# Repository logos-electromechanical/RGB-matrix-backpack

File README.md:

Logos RGB Matrix Backpack firmware, examples and docs
---------------------------

With the default firmware, this backpack is a board for driving 8x8 common anode RGB LED matrices from the I2C bus.

Remember that firmware memory is precious - you have *2 KB* of EEPROM and *128 bytes* of SRAM to work with on the backpack itself.

**Compilers:**

* AVR firmware is compiled with [WinAVR v20100110](http://sourceforge.net/projects/winavr/)

* Examples are compiled with [the Arduino IDE](http://arduino.cc/en/main/software)

**Hardware info:**

* [Holtek LED driver - HT1632C data sheet, FAQs and app notes](http://www.holtek.com/english/docum/consumer/1632c.htm)
	
* [Atmel MCU - ATtiny 2313V data sheet](http://www.atmel.com/Images/doc2543.pdf)

* [RGB LED common anode 8x8 matrix - ORM 2088RGB-5 data sheet](http://selfbuilt.net/datasheets/2088RGB-5-datasheet.jpg)

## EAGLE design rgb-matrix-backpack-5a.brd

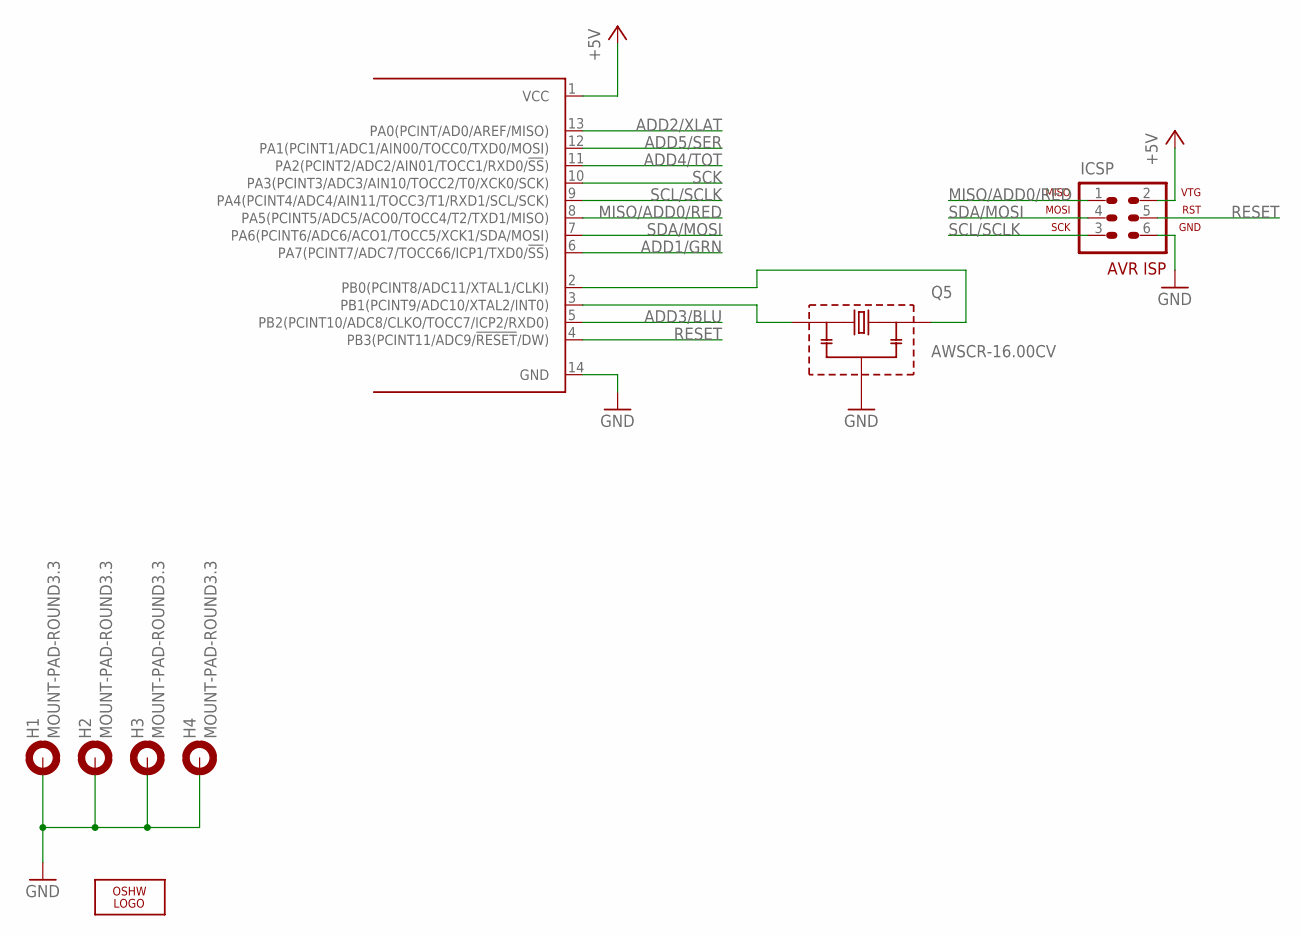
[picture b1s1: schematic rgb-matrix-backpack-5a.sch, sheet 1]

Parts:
H1, H2, H3, H4: MOUNT-PAD-ROUND3.3; 3,3-PAD
ICSP: AVR-ISP-6
LOGO1: OSHW_LOGO_FILLX0350-NT; OSHW_FILLX350_NOTEXT
Q5: AWSCR-16.00CV; AWSCR
U1: ATTINY841-SU; SO14

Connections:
ADD1/GRN: U1.6 (PA7(PCINT7/ADC7/TOCC66/ICP1/TXD0/!SS!)); also elsewhere on the board
ADD2/XLAT: U1.13 (PA0(PCINT/AD0/AREF/MISO)); also elsewhere on the board
ADD3/BLU: U1.5 (PB2(PCINT10/ADC8/CLKO/TOCC7/ICP2/RXD0)); also elsewhere on the board
ADD4/TOT: U1.11 (PA2(PCINT2/ADC2/AIN01/TOCC1/RXD0/!SS!)); also elsewhere on the board
ADD5/SER: U1.12 (PA1(PCINT1/ADC1/AIN00/TOCC0/TXD0/MOSI)); also elsewhere on the board
GND: H1.B3,3, H2.B3,3, H3.B3,3, H4.B3,3, ICSP.6, Q5.2, U1.14 (GND); also elsewhere on the board
MISO/ADD0/RED: ICSP.1, U1.8 (PA5(PCINT5/ADC5/ACO0/TOCC4/T2/TXD1/MISO)); also elsewhere on the board
unnamed: Q5.1, U1.3 (PB1(PCINT9/ADC10/XTAL2/INT0))
unnamed: Q5.3, U1.2 (PB0(PCINT8/ADC11/XTAL1/CLKI))
RESET: ICSP.5, U1.4 (PB3(PCINT11/ADC9/!RESET!/DW))
SCK: U1.10 (PA3(PCINT3/ADC3/AIN10/TOCC2/T0/XCK0/SCK)); also elsewhere on the board
SCL/SCLK: ICSP.3, U1.9 (PA4(PCINT4/ADC4/AIN11/TOCC3/T1/RXD1/SCL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); also elsewhere on the board
SDA/MOSI: ICSP.4, U1.7 (PA6(PCINT6/ADC6/ACO1/TOCC5/XCK1/SDA/MOS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); also elsewhere on the board
VCC: ICSP.2, U1.1 (VCC); also elsewhere on the board

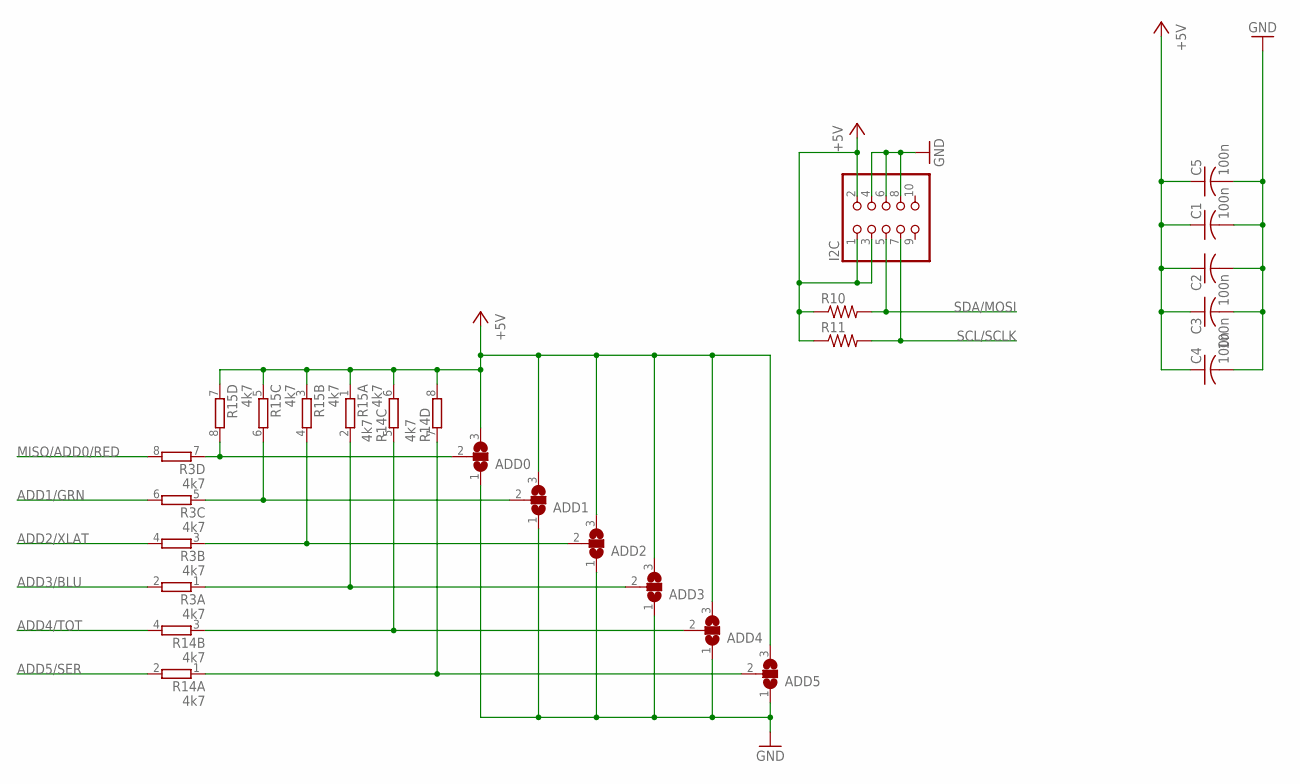
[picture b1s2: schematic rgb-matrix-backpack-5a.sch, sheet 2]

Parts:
ADD0, ADD1, ADD2, ADD3, ADD4, ADD5: SJ2W; SJ_2
C1, C2, C4, C5: 100n; C0603; PARTNO CC0603MRY5V9BB104
C3: 100n; C0603; PARTNO CC0603ZRY5V7BB105
I2C: PINHD-2X5_2.54-90°; 2X05/90
R3, R14, R15: 4k7; CTS742C083-RES; PARTNO 742C083102JPTR
R10, R11: R-US_0207/2V; 0207/2V; PARTNO CF14JT4K70

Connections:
ADD1/GRN: R3.6 (2); also elsewhere on the board
ADD2/XLAT: R3.4 (2); also elsewhere on the board
ADD3/BLU: R3.2; also elsewhere on the board
ADD4/TOT: R14.4 (2); also elsewhere on the board
ADD5/SER: R14.2; also elsewhere on the board
GND: ADD0.1, ADD1.1, ADD2.1, ADD3.1, ADD4.1, ADD5.1, C1.2, C2.2, C3.2, C4.2, C5.2, I2C.4, I2C.6, I2C.8; also elsewhere on the board
MISO/ADD0/RED: R3.8 (2); also elsewhere on the board
unnamed: ADD3.2, R3.1, R15.2
unnamed: ADD2.2, R3.3 (1), R15.4 (2)
unnamed: ADD0.2, R3.7 (1), R15.8 (2)
unnamed: ADD1.2, R3.5 (1), R15.6 (2)
unnamed: ADD4.2, R14.3 (1), R14.5 (1)
unnamed: ADD5.2, R14.1, R14.7 (1)
SCL/SCLK: I2C.7, R11.2; also elsewhere on the board
SDA/MOSI: I2C.5, R10.2; also elsewhere on the board
VCC: ADD0.3, ADD1.3, ADD2.3, ADD3.3, ADD4.3, ADD5.3, C1.1, C2.1, C3.1, C4.1, C5.1, I2C.1, I2C.2, I2C.3, R10.1, R11.1, R14.6 (2), R14.8 (2), R15.1, R15.3 (1), R15.5 (1), R15.7 (1); also elsewhere on the board

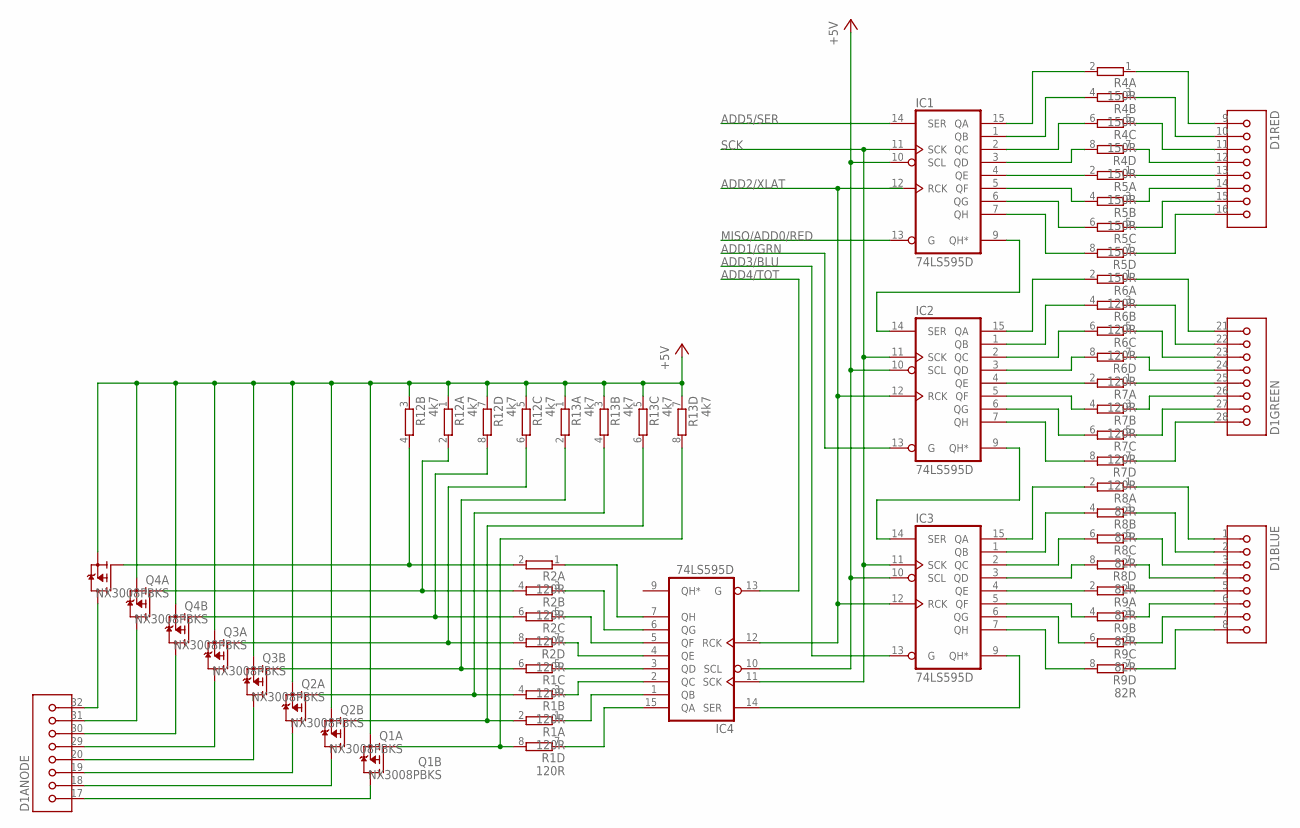
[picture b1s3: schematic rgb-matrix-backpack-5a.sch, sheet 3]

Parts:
D1: 60MM-8X8-RGB-LED-ARRAY; 60MM-8X8-RGB-MATRIX
IC1, IC2, IC3, IC4: 74LS595D; SO16
Q1: NX3008PBKS; SOT363_INFINEON; PARTNO NX3008PBKS
Q2, Q3, Q4: NX3008PBKS; SOT363_INFINEON
R1, R2, R6, R7: 120R; CTS742C083-RES; PARTNO 742C083102JPTR
R4, R5: 150R; CTS742C083-RES; PARTNO 742C083102JPTR
R8, R9: 82R; CTS742C083-RES; PARTNO 742C083102JPTR
R12, R13: 4k7; CTS742C083-RES; PARTNO 742C083102JPTR

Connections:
ADD1/GRN: IC2.13 (G); also elsewhere on the board
ADD2/XLAT: IC1.12 (RCK), IC2.12 (RCK), IC3.12 (RCK), IC4.12 (RCK); also elsewhere on the board
ADD3/BLU: IC3.13 (G); also elsewhere on the board
ADD4/TOT: IC4.13 (G); also elsewhere on the board
ADD5/SER: IC1.14 (SER); also elsewhere on the board
GND: IC1.8 (GND), IC2.8 (GND), IC3.8 (GND), IC4.8 (GND); also elsewhere on the board
MISO/ADD0/RED: IC1.13 (G); also elsewhere on the board
unnamed: D1.9 (1), R4.1
unnamed: D1.10 (2), R4.3 (1)
unnamed: D1.11 (3), R4.5 (1)
unnamed: D1.12 (4), R4.7 (1)
unnamed: D1.13 (5), R5.1
unnamed: D1.14 (6), R5.3 (1)
unnamed: D1.15 (7), R5.5 (1)
unnamed: D1.16 (8), R5.7 (1)
unnamed: D1.1, R8.1
unnamed: D1.2, R8.3 (1)
unnamed: D1.3, R8.5 (1)
unnamed: D1.4, R8.7 (1)
unnamed: D1.5, R9.1
unnamed: D1.6, R9.3 (1)
unnamed: D1.7, R9.5 (1)
unnamed: D1.8, R9.7 (1)
unnamed: D1.21 (8), R6.1
unnamed: D1.22 (7), R6.3 (1)
unnamed: D1.23 (6), R6.5 (1)
unnamed: D1.24 (5), R6.7 (1)
unnamed: D1.25 (4), R7.1
unnamed: D1.26 (3), R7.3 (1)
unnamed: D1.27 (2), R7.5 (1)
unnamed: D1.28 (1), R7.7 (1)
unnamed: IC3.9 (QH*), IC4.14 (SER)
unnamed: IC1.15 (QA), R4.2
unnamed: IC1.2 (QC), R4.6 (2)
unnamed: IC1.4 (QE), R5.2
unnamed: IC1.6 (QG), R5.6 (2)
unnamed: IC2.15 (QA), R6.2
unnamed: IC2.2 (QC), R6.6 (2)
unnamed: IC2.4 (QE), R7.2
unnamed: IC2.6 (QG), R7.6 (2)
unnamed: IC3.1 (QB), R8.4 (2)
unnamed: IC3.3 (QD), R8.8 (2)
unnamed: IC3.5 (QF), R9.4 (2)
unnamed: IC3.7 (QH), R9.8 (2)
unnamed: IC1.3 (QD), R4.8 (2)
unnamed: IC1.5 (QF), R5.4 (2)
unnamed: IC2.1 (QB), R6.4 (2)
unnamed: IC2.3 (QD), R6.8 (2)
unnamed: IC2.5 (QF), R7.4 (2)
unnamed: IC2.7 (QH), R7.8 (2)
unnamed: IC3.15 (QA), R8.2
unnamed: IC3.2 (QC), R8.6 (2)
unnamed: IC3.4 (QE), R9.2
unnamed: IC3.6 (QG), R9.6 (2)
unnamed: IC4.15 (QA), R1.7 (1)
unnamed: IC4.1 (QB), R1.1
unnamed: IC4.2 (QC), R1.3 (1)
unnamed: IC4.3 (QD), R1.5 (1)
unnamed: Q1.5 (G), R1.8 (2), R13.8 (2)
unnamed: IC1.7 (QH), R5.8 (2)
unnamed: Q1.2 (G), R1.2, R13.6 (2)
unnamed: IC1.9 (QH*), IC2.14 (SER)
unnamed: IC2.9 (QH*), IC3.14 (SER)
unnamed: Q2.2 (G), R1.6 (2), R13.2
unnamed: Q2.5 (G), R1.4 (2), R13.4 (2)
unnamed: IC1.1 (QB), R4.4 (2)
unnamed: D1.20 (4), Q2.6 (D)
unnamed: D1.19 (3), Q2.3 (D)
unnamed: D1.18 (2), Q1.6 (D)
unnamed: D1.17 (1), Q1.3 (D)
unnamed: D1.29 (5), Q3.3 (D)
unnamed: D1.30 (6), Q3.6 (D)
unnamed: D1.31 (7), Q4.3 (D)
unnamed: D1.32 (8), Q4.6 (D)
unnamed: IC4.4 (QE), R2.7 (1)
unnamed: IC4.5 (QF), R2.5 (1)
unnamed: IC4.6 (QG), R2.3 (1)
unnamed: IC4.7 (QH), R2.1
unnamed: Q4.2 (G), R2.2, R12.4 (2)
unnamed: Q4.5 (G), R2.4 (2), R12.2
unnamed: Q3.2 (G), R2.6 (2), R12.8 (2)
unnamed: Q3.5 (G), R2.8 (2), R12.6 (2)
SCK: IC1.11 (SCK), IC2.11 (SCK), IC3.11 (SCK), IC4.11 (SCK); also elsewhere on the board
VCC: IC1.10 (SCL), IC1.16 (VCC), IC2.10 (SCL), IC2.16 (VCC), IC3.10 (SCL), IC3.16 (VCC), IC4.10 (SCL), IC4.16 (VCC), Q1.1 (S), Q1.4 (S), Q2.1 (S), Q2.4 (S), Q3.1 (S), Q3.4 (S), Q4.1 (S), Q4.4 (S), R12.1, R12.3 (1), R12.5 (1), R12.7 (1), R13.1, R13.3 (1), R13.5 (1), R13.7 (1); also elsewhere on the board

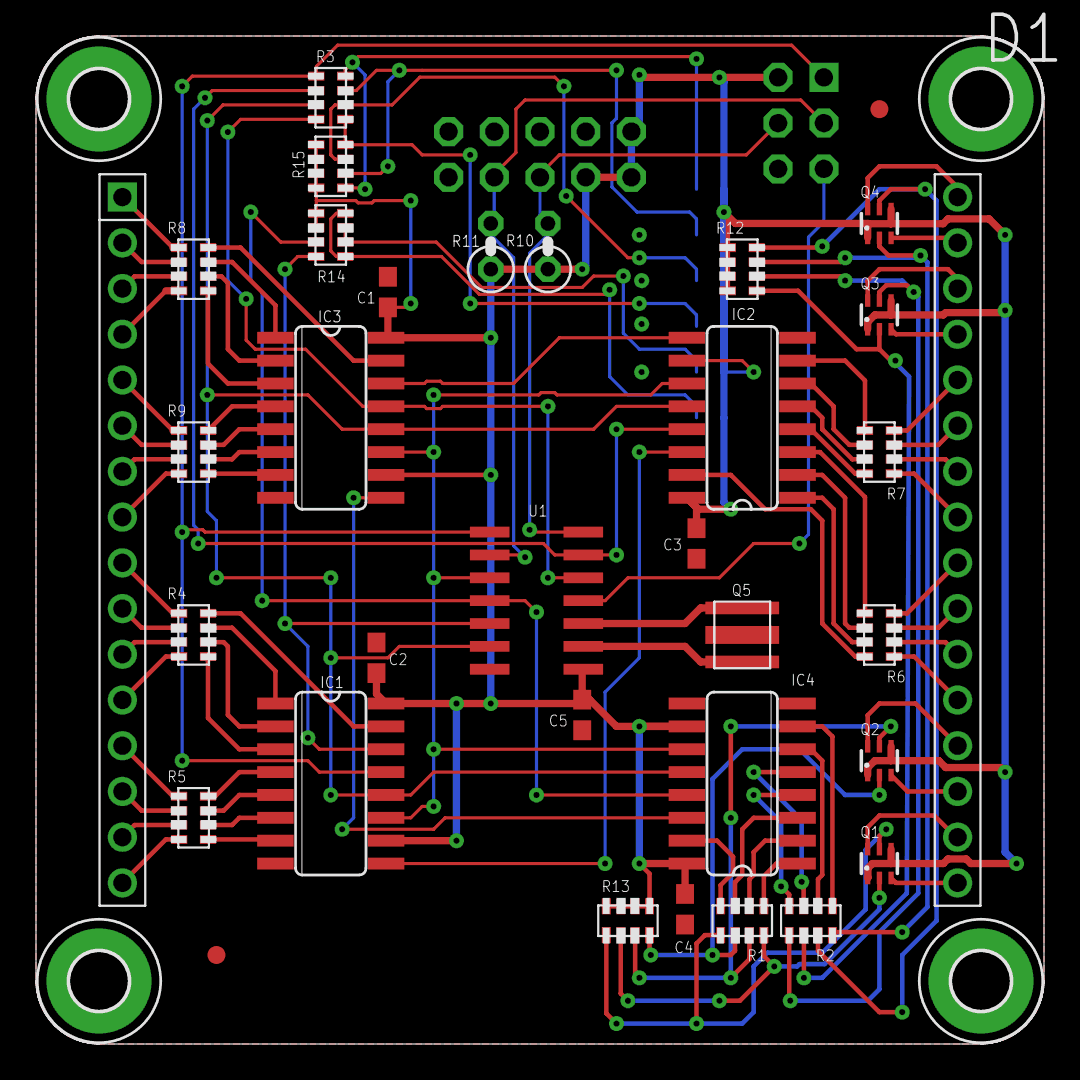
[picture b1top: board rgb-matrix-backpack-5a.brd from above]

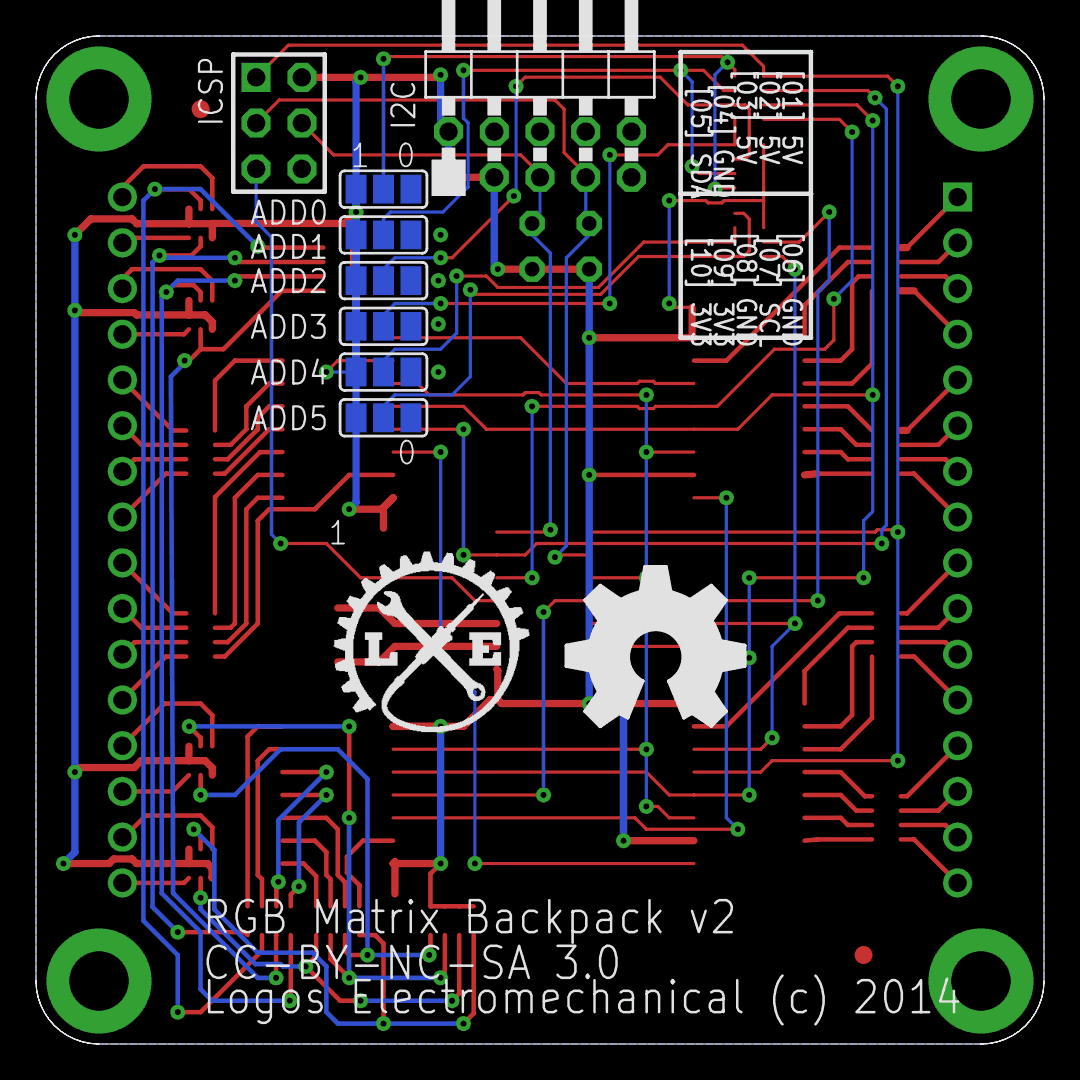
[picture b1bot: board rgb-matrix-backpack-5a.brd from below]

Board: 2 copper layers, 56.0 x 56.0 mm, 47 parts (10 on the bottom side), 95 nets.

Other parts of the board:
U$1: LOGO-SM
U$4, U$5: FIDUCIAL_G10

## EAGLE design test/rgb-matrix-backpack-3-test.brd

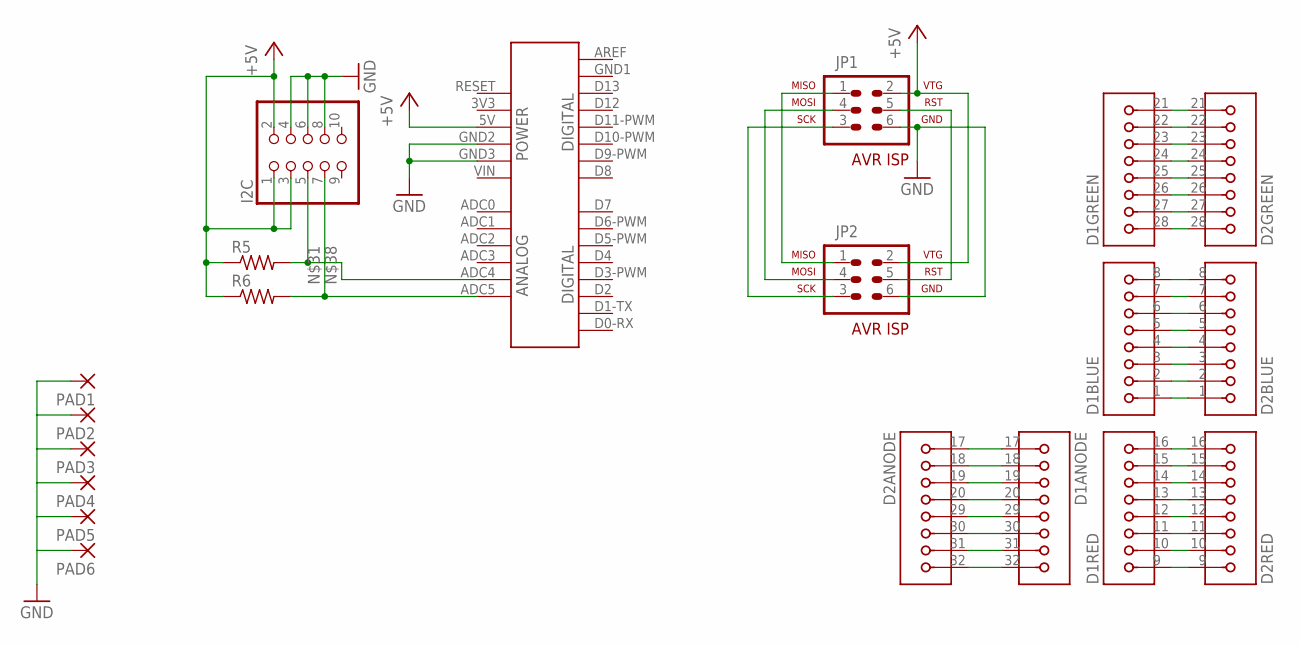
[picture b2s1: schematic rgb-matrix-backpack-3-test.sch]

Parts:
D1, D2: 60MM-8X8-RGB-LED-ARRAY; 60MM-8X8-RGB-MATRIX
I2C: PINHD-2X5_2.54-90°; 2X05/90
JP1, JP2: AVR-ISP-6
PAD1, PAD2, PAD3, PAD4, PAD5, PAD6: 1,6/0,8
R5, R6: R-US_R0603; R0603
SHIELD1: 2009

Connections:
+5V: I2C.1, I2C.2, I2C.3, JP1.2, JP2.2, R5.1, R6.1, SHIELD1.5V
GND: I2C.4, I2C.6, I2C.8, JP1.6, JP2.6, PAD1.1, PAD2.1, PAD3.1, PAD4.1, PAD5.1, PAD6.1, SHIELD1.GND2, SHIELD1.GND3
unnamed: D1.17 (1), D2.17 (1)
unnamed: D1.18 (2), D2.18 (2)
unnamed: D1.19 (3), D2.19 (3)
unnamed: D1.20 (4), D2.20 (4)
unnamed: D1.29 (5), D2.29 (5)
unnamed: D1.30 (6), D2.30 (6)
unnamed: D1.31 (7), D2.31 (7)
unnamed: D1.32 (8), D2.32 (8)
unnamed: D1.1, D2.1
unnamed: D1.2, D2.2
unnamed: D1.3, D2.3
unnamed: D1.4, D2.4
unnamed: D1.5, D2.5
unnamed: D1.6, D2.6
unnamed: D1.7, D2.7
unnamed: D1.8, D2.8
unnamed: D1.9 (1), D2.9 (1)
unnamed: D1.10 (2), D2.10 (2)
unnamed: D1.11 (3), D2.11 (3)
unnamed: D1.12 (4), D2.12 (4)
unnamed: D1.13 (5), D2.13 (5)
unnamed: D1.14 (6), D2.14 (6)
unnamed: D1.15 (7), D2.15 (7)
unnamed: D1.16 (8), D2.16 (8)
unnamed: D1.28 (1), D2.28 (1)
unnamed: D1.27 (2), D2.27 (2)
unnamed: D1.26 (3), D2.26 (3)
unnamed: JP1.1, JP2.1
unnamed: D1.25 (4), D2.25 (4)
unnamed: D1.24 (5), D2.24 (5)
unnamed: I2C.5, R5.2, SHIELD1.ADC4
unnamed: D1.23 (6), D2.23 (6)
unnamed: D1.22 (7), D2.22 (7)
unnamed: D1.21 (8), D2.21 (8)
unnamed: JP1.5, JP2.5
unnamed: I2C.7, R6.2, SHIELD1.ADC5
SCL: JP1.3, JP2.3
SDA: JP1.4, JP2.4

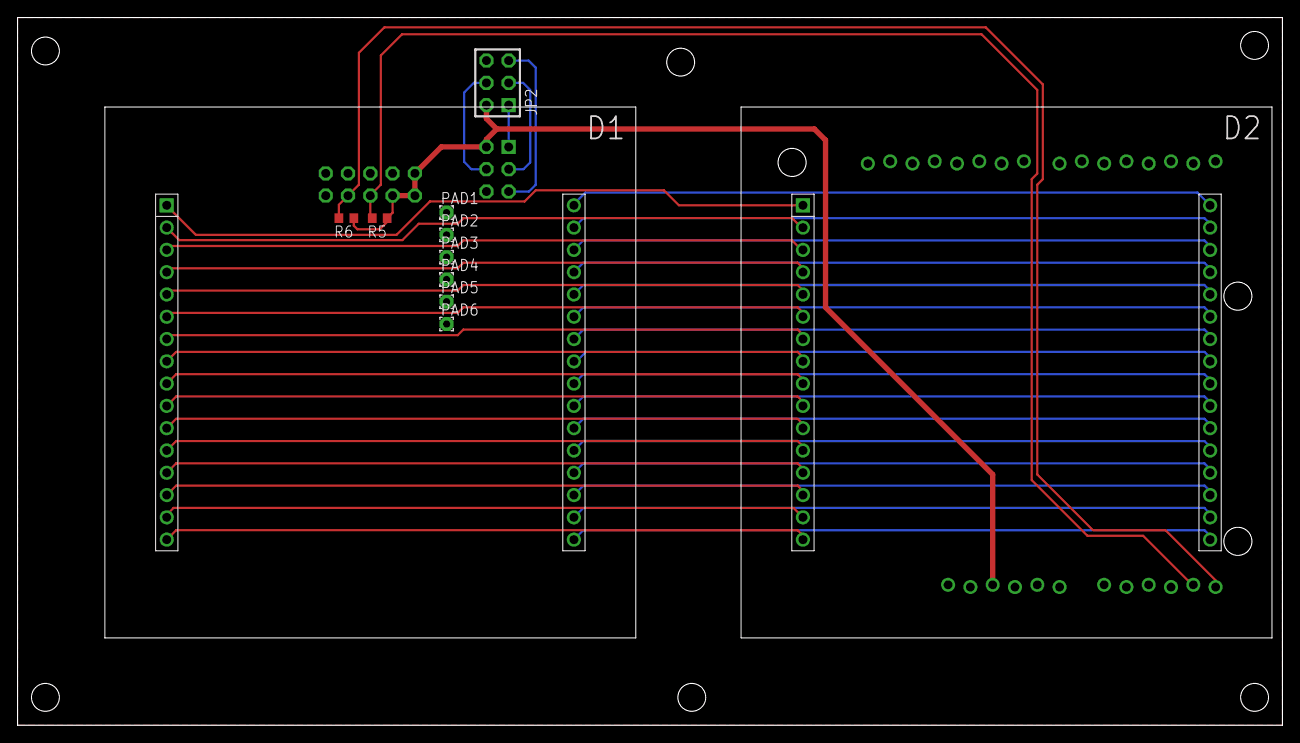
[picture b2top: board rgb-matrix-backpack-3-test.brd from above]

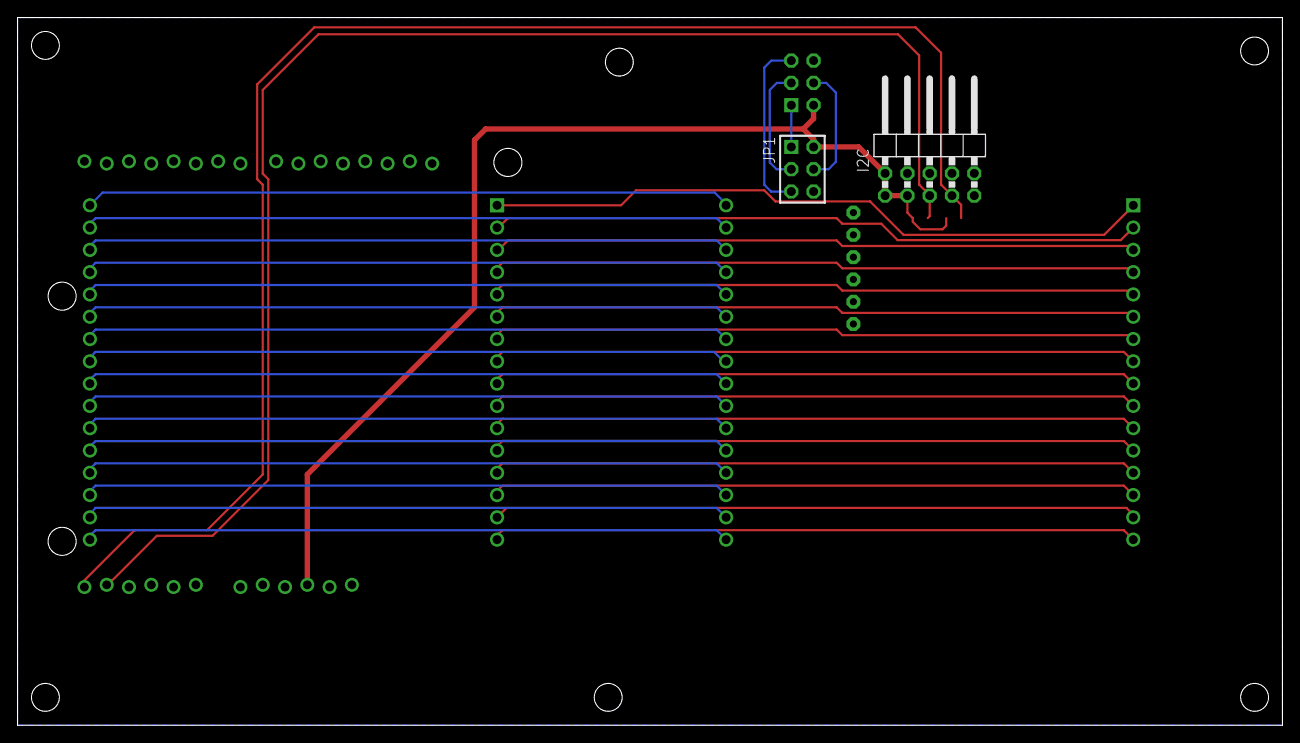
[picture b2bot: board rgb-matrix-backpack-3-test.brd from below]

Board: 2 copper layers, 144.1 x 80.6 mm, 14 parts (2 on the bottom side), 40 nets.

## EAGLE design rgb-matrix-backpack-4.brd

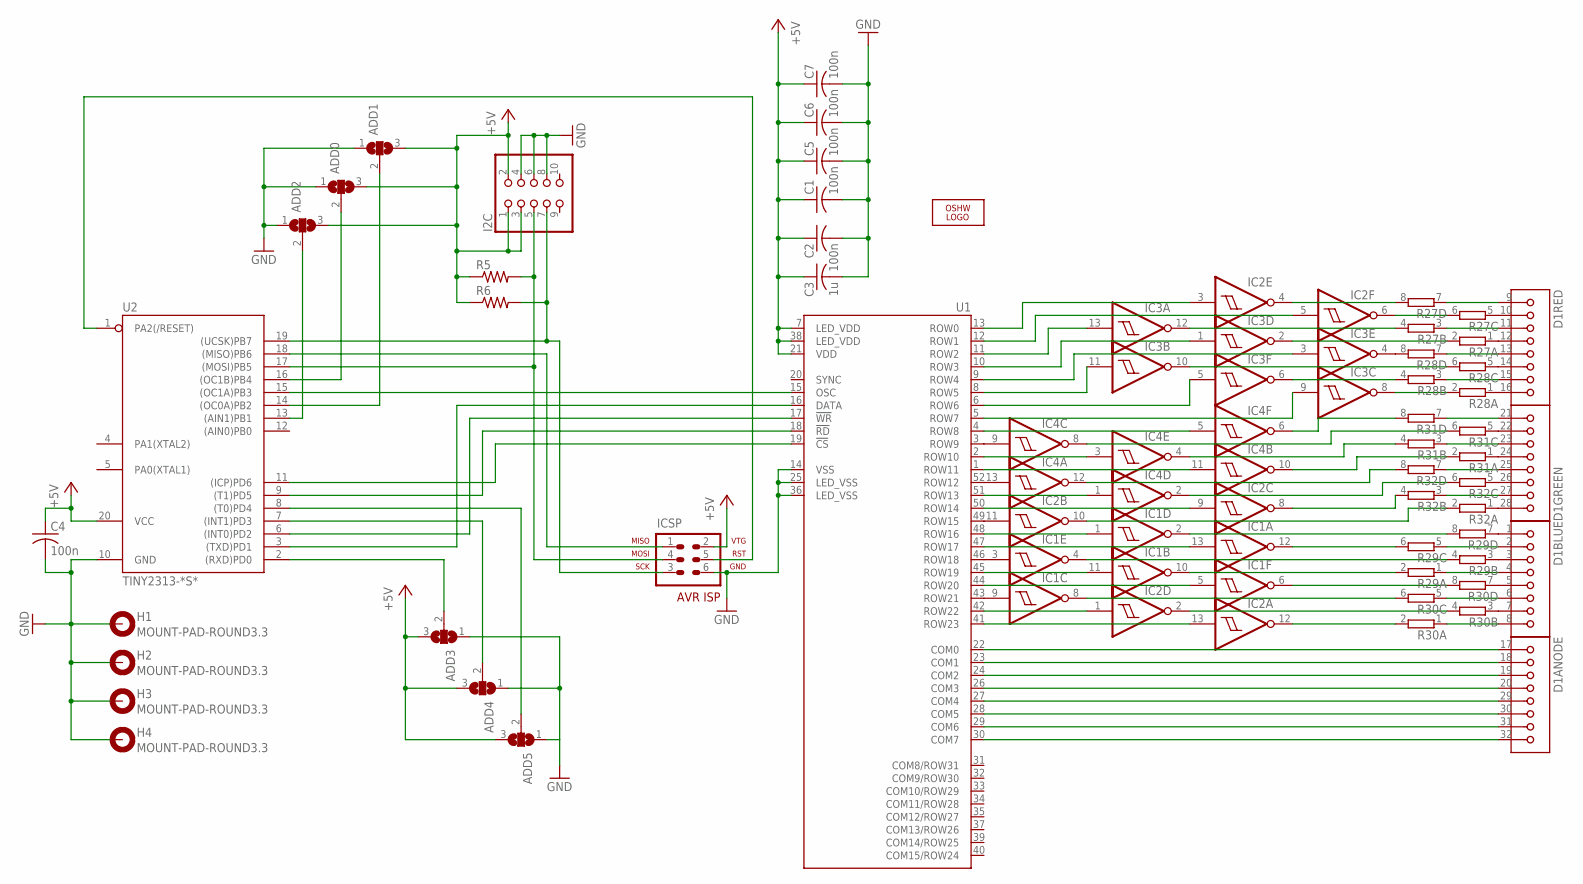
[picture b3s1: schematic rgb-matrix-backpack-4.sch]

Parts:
ADD0, ADD1, ADD2, ADD3, ADD4, ADD5: SJ2W; SJ_2
C1, C2, C4, C5, C6, C7: 100n; C0603; PARTNO CC0603MRY5V9BB104
C3: 1u; C0603; PARTNO CC0603ZRY5V7BB105
D1: 60MM-8X8-RGB-LED-ARRAY; 60MM-8X8-RGB-MATRIX
H1, H2, H3, H4: MOUNT-PAD-ROUND3.3; 3,3-PAD
I2C: PINHD-2X5_2.54-90°; 2X05/90
IC1, IC2, IC3, IC4: 74AC14D; SO14; PARTNO SN74AC14D
ICSP: AVR-ISP-6
LOGO1: OSHW_LOGO_FILLX0350-NT; OSHW_FILLX350_NOTEXT
R5, R6: R-US_0207/2V; 0207/2V; PARTNO CF14JT4K70
R27, R28, R29, R30, R31, R32: 4R-NCTS742C083; CTS742C083-RES; PARTNO 742C083102JPTR
U1: HT1632C; QFP52_SOT379-1; PARTNO HT1632C
U2: TINY2313-*S*; SO20L$; PARTNO ATTINY2313V-10SU

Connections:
GND: ADD0.1, ADD1.1, ADD2.1, ADD3.1, ADD4.1, ADD5.1, C1.2, C2.2, C3.2, C4.2, C5.2, C6.2, C7.2, H1.B3,3, H2.B3,3, H3.B3,3, H4.B3,3, I2C.4, I2C.6, I2C.8, IC1.7 (GND), IC2.7 (GND), IC3.7 (GND), IC4.7 (GND), ICSP.6, U1.14 (VSS), U1.25 (LED_VSS), U1.36 (LED_VSS), U2.10 (GND)
unnamed: D1.9 (1), R27.7 (1)
unnamed: D1.10 (2), R27.5 (1)
unnamed: D1.11 (3), R27.3 (1)
unnamed: D1.12 (4), R27.1
unnamed: D1.13 (5), R28.7 (1)
unnamed: D1.14 (6), R28.5 (1)
unnamed: D1.15 (7), R28.3 (1)
unnamed: D1.16 (8), R28.1
unnamed: D1.1, R29.7 (1)
unnamed: D1.2, R29.5 (1)
unnamed: D1.3, R29.3 (1)
unnamed: D1.4, R29.1
unnamed: D1.5, R30.7 (1)
unnamed: D1.6, R30.5 (1)
unnamed: D1.7, R30.3 (1)
unnamed: D1.8, R30.1
unnamed: D1.21 (8), R31.7 (1)
unnamed: D1.22 (7), R31.5 (1)
unnamed: D1.23 (6), R31.3 (1)
unnamed: D1.24 (5), R31.1
unnamed: D1.25 (4), R32.7 (1)
unnamed: D1.26 (3), R32.5 (1)
unnamed: D1.27 (2), R32.3 (1)
unnamed: D1.28 (1), R32.1
unnamed: D1.17 (1), U1.22 (COM0)
unnamed: D1.18 (2), U1.23 (COM1)
unnamed: D1.19 (3), U1.24 (COM2)
unnamed: ICSP.1, U2.18 ((MISO)PB6)
unnamed: U1.15 (OSC), U2.15 ((OC1A)PB3)
unnamed: D1.20 (4), U1.26 (COM3)
unnamed: ICSP.5, U2.1 (PA2(/RESET))
unnamed: IC2.12 (O), R30.2
unnamed: D1.29 (5), U1.27 (COM4)
unnamed: ADD3.2, U2.2 ((RXD)PD0)
unnamed: ADD4.2, U2.7 ((INT1)PD3)
unnamed: I2C.5, ICSP.4, R5.2, U2.17 ((MOSI)PB5)
unnamed: I2C.7, ICSP.3, R6.2, U2.19 ((UCSK)PB7)
unnamed: D1.30 (6), U1.28 (COM5)
unnamed: ADD5.2, U2.8 ((T0)PD4)
unnamed: D1.31 (7), U1.29 (COM6)
unnamed: D1.32 (8), U1.30 (COM7)
unnamed: IC2.2 (O), R30.4 (2)
unnamed: IC1.8 (O), R30.6 (2)
unnamed: IC1.6 (O), R30.8 (2)
unnamed: IC1.10 (O), R29.2
unnamed: IC1.4 (O), R29.4 (2)
unnamed: IC1.12 (O), R29.6 (2)
unnamed: U1.16 (DATA), U2.3 ((TXD)PD1)
unnamed: U1.17 (!WR!), U2.6 ((INT0)PD2)
unnamed: U1.18 (!RD!), U2.9 ((T1)PD5)
unnamed: U1.19 (!CS!), U2.11 ((ICP)PD6)
unnamed: IC1.2 (O), R29.8 (2)
unnamed: IC3.8 (O), R28.2
unnamed: IC3.6 (O), R28.4 (2)
unnamed: IC3.10 (O), R28.6 (2)
unnamed: IC3.4 (O), R28.8 (2)
unnamed: IC3.2 (O), R27.2
unnamed: IC3.12 (O), R27.4 (2)
unnamed: IC2.6 (O), R27.6 (2)
unnamed: IC2.4 (O), R27.8 (2)
unnamed: IC4.8 (O), R31.6 (2)
unnamed: IC4.6 (O), R31.8 (2)
unnamed: IC4.4 (O), R31.4 (2)
unnamed: IC4.10 (O), R31.2
unnamed: IC4.12 (O), R32.8 (2)
unnamed: IC4.2 (O), R32.6 (2)
unnamed: IC2.8 (O), R32.4 (2)
unnamed: IC2.10 (O), R32.2
unnamed: IC3.1 (I), U1.10 (ROW3)
unnamed: IC3.9 (I), U1.5 (ROW7)
unnamed: IC3.5 (I), U1.6 (ROW6)
unnamed: IC3.11 (I), U1.8 (ROW5)
unnamed: ADD2.2, U2.13 ((AIN1)PB1)
unnamed: IC3.3 (I), U1.9 (ROW4)
unnamed: IC3.13 (I), U1.11 (ROW2)
unnamed: IC2.5 (I), U1.12 (ROW1)
unnamed: ADD0.2, U2.16 ((OC1B)PB4)
unnamed: ADD1.2, U2.14 ((OC0A)PB2)
unnamed: IC2.3 (I), U1.13 (ROW0)
unnamed: IC2.13 (I), U1.41 (ROW23)
unnamed: IC2.1 (I), U1.42 (ROW22)
unnamed: IC1.9 (I), U1.43 (ROW21)
unnamed: IC1.3 (I), U1.46 (ROW18)
unnamed: IC1.11 (I), U1.45 (ROW19)
unnamed: IC1.5 (I), U1.44 (ROW20)
unnamed: IC1.13 (I), U1.47 (ROW17)
unnamed: IC1.1 (I), U1.48 (ROW16)
unnamed: IC4.3 (I), U1.2 (ROW10)
unnamed: IC4.5 (I), U1.4 (ROW8)
unnamed: IC4.9 (I), U1.3 (ROW9)
unnamed: IC4.11 (I), U1.1 (ROW11)
unnamed: IC4.13 (I), U1.52 (ROW12)
unnamed: IC4.1 (I), U1.51 (ROW13)
unnamed: IC2.9 (I), U1.50 (ROW14)
unnamed: IC2.11 (I), U1.49 (ROW15)
VCC: ADD0.3, ADD1.3, ADD2.3, ADD3.3, ADD4.3, ADD5.3, C1.1, C2.1, C3.1, C4.1, C5.1, C6.1, C7.1, I2C.1, I2C.2, I2C.3, IC1.14 (VCC), IC2.14 (VCC), IC3.14 (VCC), IC4.14 (VCC), ICSP.2, R5.1, R6.1, U1.7 (LED_VDD), U1.21 (VDD), U1.38 (LED_VDD), U2.20 (VCC)

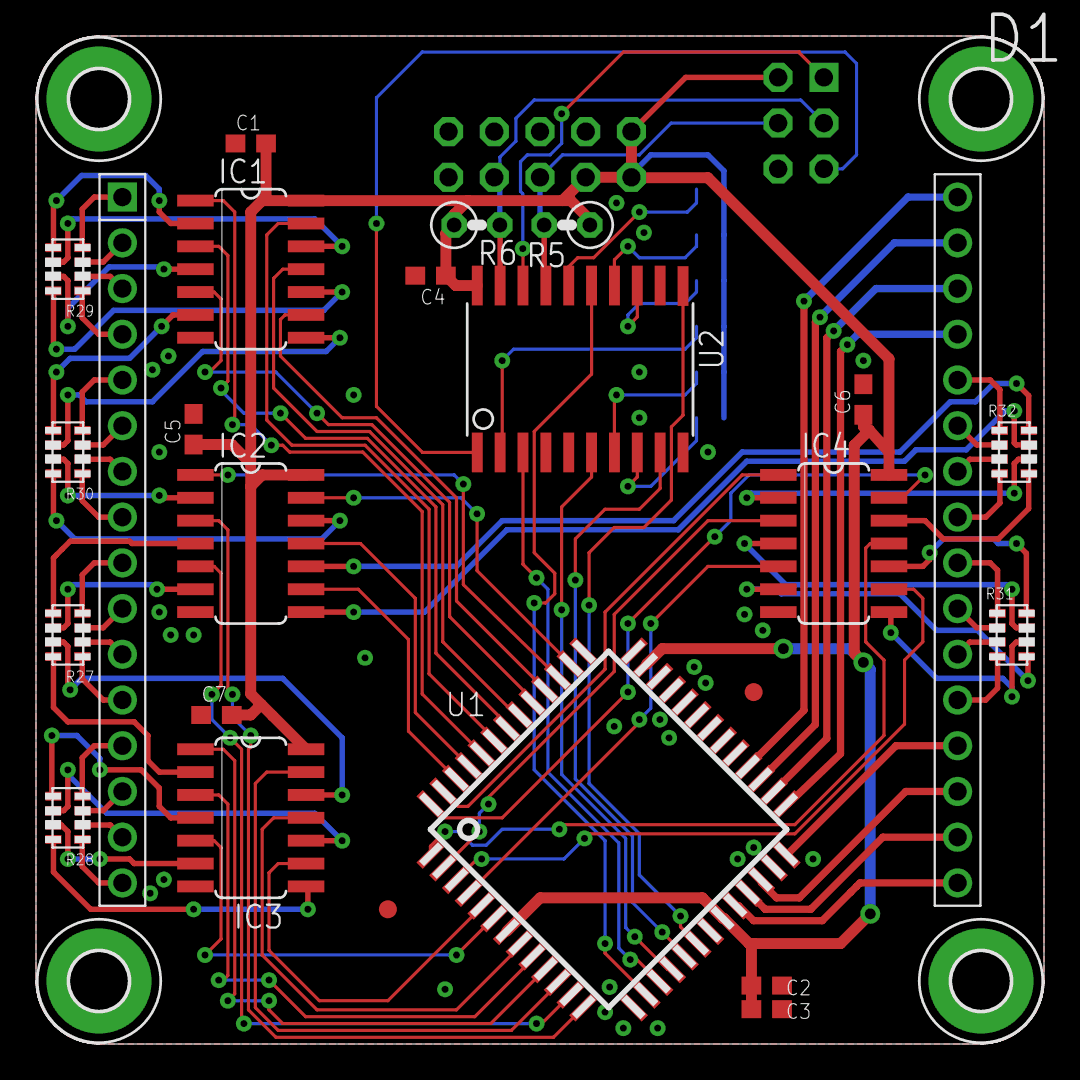
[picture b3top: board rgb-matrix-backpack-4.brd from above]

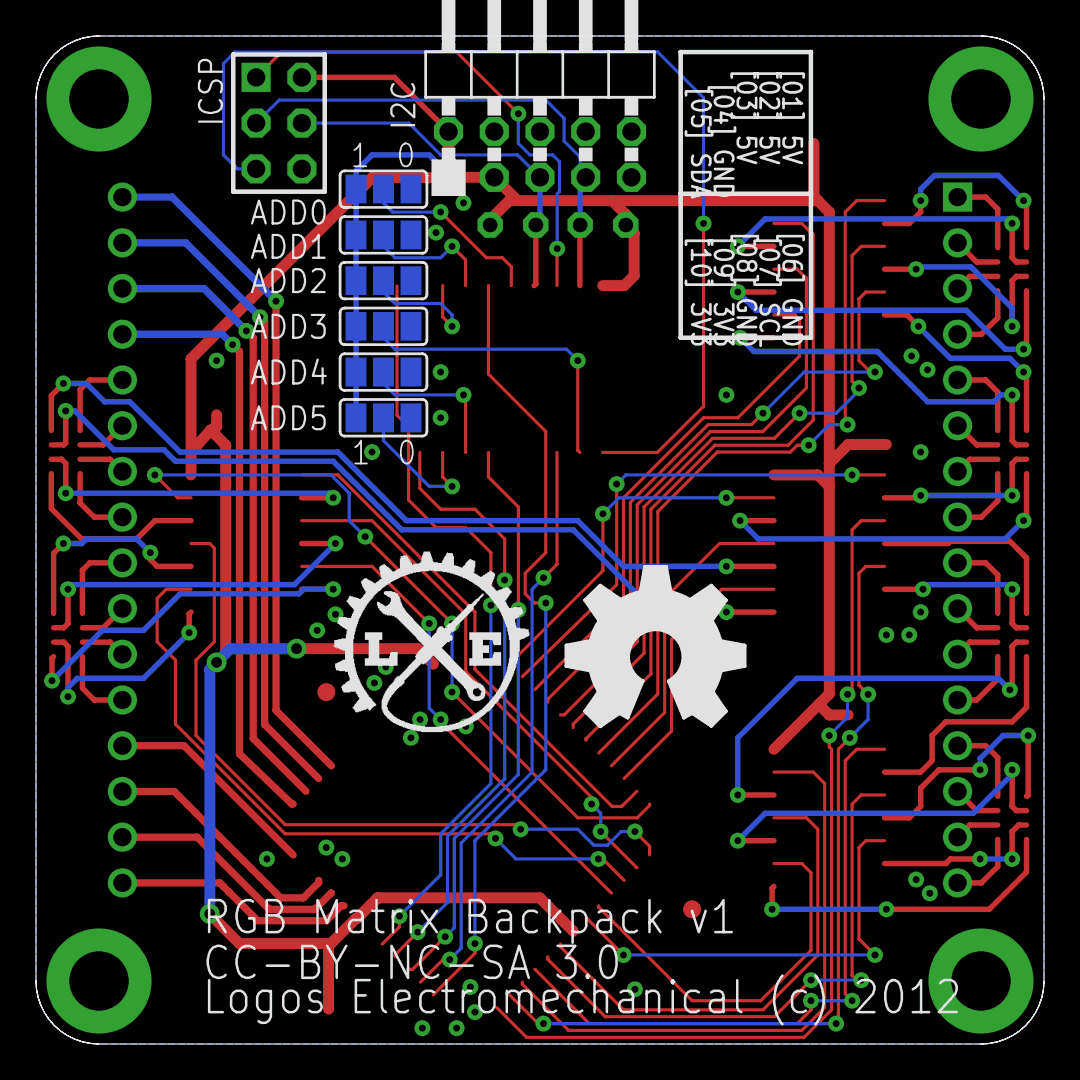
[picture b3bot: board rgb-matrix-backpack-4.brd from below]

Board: 2 copper layers, 56.0 x 56.0 mm, 38 parts (10 on the bottom side), 97 nets.

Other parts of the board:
U$1: LOGO-SM
U$4, U$5: FIDUCIAL_G10

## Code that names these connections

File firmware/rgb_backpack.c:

// low fuse setting:		0xef
// high fuse setting:		0xdf
// extended fuse setting: 	0xff
// avrdude fuse command line: "avrdude -c usbtiny -p t2313 -Ulfuse:w:0xe4:m -Uhfuse:w:0xdf:m -Uefuse:w:0xff:m"
// avrdude flash command line: "avrdude  -c usbtiny -p t2313 -Uflash:w:rgb_backpack.hex"
// avrdude whole command line: "avrdude -c usbtiny -p t2313 -Ulfuse:w:0xe4:m -Uhfuse:w:0xdf:m -Uefuse:w:0xff:m -Uflash:w:rgb_backpack.hex"

#include <avr/io.h>    		// for PORTx, PINx, DDRx, etc.
#include <avr/interrupt.h>  // there will be interrupts
#include <stdint.h>			// for all those tasty integer types
#include <avr/sfr_defs.h>	// some useful stuff for manipulation of registers
#include <util/delay.h>
#include <util/twi.h>		// bitmask for I2C
#include "usiTwiSlave.h"

// Define the address setting jumpers

#define ADDL_PORT	PINB
#define ADDH_PORT	PIND

// Define the lines for driving the backpack chip

#define DRV_PORT 	PORTD
#define DRV_CS		PD6
#define DRV_RD		PD5
#define DRV_WR		PD2
#define DRV_DATA	PD1

// Define commands

#define CMD_DISABLE		0x00
#define CMD_ENABLE		0x01
#define CMD_LEDOFF		0x02
#define CMD_LEDON		0x03
#define CMD_BLINKON		0x08
#define CMD_BLINKOFF	0x09
#define CMD_SLAVE		0x10
#define CMD_MASTER_RC	0x18
#define CMD_MASTER_EXT	0x1c
#define CMD_COM_N8		0x20
#define CMD_COM_N16		0x24
#define CMD_COM_P8		0x28
#define CMD_COM_P16		0x2c

void init (void);
void shiftOut (uint8_t *bytes); 
void shiftCmd (uint8_t cmd);
void shiftByte (uint8_t byte);
void shiftBuffer (void);

int main (void) {

	
	init();
	
	while (1) {
		if(usiTwiDataInReceiveBuffer()) {
			_delay_ms(10.0);
			shiftBuffer();
		}
	}
	
}

void init (void) {
	uint8_t address = 0x00;
	//uint8_t bytes[24] = {0,0,0,0,0,0,0,0,0,0,0,0,0,0,0,0,0,0,0,0,0,0,0,0};
	
	// set up ports
	DDRD = 0xe6;
	DDRB = 0xe9;
	
	// initialize driver
	DRV_PORT |= (_BV(DRV_CS) | _BV(DRV_WR) | _BV(DRV_RD) | _BV(DRV_DATA));
	//shiftCmd(CMD_MASTER_RC);
	shiftCmd(CMD_MASTER_EXT);
	shiftCmd(CMD_COM_P8);
	shiftCmd(CMD_ENABLE);
	shiftCmd(CMD_LEDON);
	
	// start the timer
	TCCR1A 	= _BV(COM1A0);					// Toggle on match, channel A
	TCCR1B 	= _BV(WGM12) | _BV(CS10);		// CTC mode, no prescaling
	OCR1A	= 3;							// 1 MHz		
	
	// read address
	PORTB |= (_BV(PB4)|_BV(PB2)|_BV(PB1));			// set pullups high to enable default address
	PORTD |= (_BV(PD0)|_BV(PD3)|_BV(PD4));			// set pullups high to enable default address
	if ((PINB & _BV(PB4)) != 0) address |= 0x01; 
	if ((PINB & _BV(PB2)) != 0) address |= 0x02;
	if ((PINB & _BV(PB1)) != 0) address |= 0x04;
	if ((PIND & _BV(PD0)) != 0) address |= 0x08; 
	if ((PIND & _BV(PD3)) != 0) address |= 0x10;
	if ((PIND & _BV(PD4)) != 0) address |= 0x20;
	address |= 0x40;	// set the high bit, so we don't squat on the broadcast address (0x00)
	
	// check address
	//bytes[0] = address;
	//bytes[1] = ~address;
	//shiftOut(bytes);
	
	// initialize USI for I2C slave
	usiTwiSlaveInit(address);
	
	// enable interrupts
	sei();
	return;
}

void shiftOut (uint8_t *bytes) {

	uint8_t i, j, val;
	
	DRV_PORT &= ~_BV(DRV_CS);		// enable the serial bus
	DRV_PORT &= ~_BV(DRV_WR);
	DRV_PORT |= _BV(DRV_WR);		// clock in a one
	DRV_PORT &= ~_BV(DRV_DATA);	// set data output to zero
	DRV_PORT &= ~_BV(DRV_WR);
	DRV_PORT |= _BV(DRV_WR);		// clock in a zero
	DRV_PORT |= _BV(DRV_DATA);
	DRV_PORT &= ~_BV(DRV_WR);
	DRV_PORT |= _BV(DRV_WR);		// clock in a one	
	DRV_PORT &= ~_BV(DRV_DATA);	// set data output to zero
	DRV_PORT &= ~_BV(DRV_WR);
	
	// set the address to 0x00
	for (i = 0; i < 7; i++)  {
		DRV_PORT &= ~_BV(DRV_WR);
		DRV_PORT |= _BV(DRV_WR);
	}
	
	// shift the data
	for (i = 0; i < 24; i++) {
		val = bytes[i];
		for (j = 0; j < 8; j++)  {
			DRV_PORT &= ~_BV(DRV_WR);	// prep for next bit
			if (val & (1 << j)) {
				DRV_PORT |= _BV(DRV_DATA);
			} else {
				DRV_PORT &= ~_BV(DRV_DATA);
			}
			DRV_PORT |= _BV(DRV_WR);	// clock in the next bit
		}
	}
	DRV_PORT |= _BV(DRV_WR);
	DRV_PORT |= _BV(DRV_DATA);
	DRV_PORT |= _BV(DRV_CS);		// end transmission
	return;
}

void shiftCmd (uint8_t cmd) {
	uint8_t i;

	DRV_PORT &= ~_BV(DRV_CS);		// enable the serial bus
	_delay_us(1.0);	
	DRV_PORT &= ~_BV(DRV_WR);
	_delay_us(1.0);
	DRV_PORT |= _BV(DRV_WR);		// clock in a one
	_delay_us(1.0);
	DRV_PORT &= ~_BV(DRV_DATA);	// set data output to zero
	DRV_PORT &= ~_BV(DRV_WR);
	_delay_us(1.0);
	DRV_PORT |= _BV(DRV_WR);		// clock in a zero
	_delay_us(1.0);
	DRV_PORT &= ~_BV(DRV_WR);
	_delay_us(1.0);
	DRV_PORT |= _BV(DRV_WR);		// clock in a zero

	for (i = 0; i < 8; i++)  {
		DRV_PORT &= ~_BV(DRV_WR);	// prep for next bit
		if (cmd & (1 << (7 - i))) {
			DRV_PORT |= _BV(DRV_DATA);
		} else {
			DRV_PORT &= ~_BV(DRV_DATA);
		}
		_delay_us(1.0);
		DRV_PORT |= _BV(DRV_WR);	// clock in the next bit
		_delay_us(1.0);
	}
	DRV_PORT &= ~_BV(DRV_DATA);	// set data output to zero
	DRV_PORT &= ~_BV(DRV_WR);
	_delay_us(1.0);
	DRV_PORT |= _BV(DRV_WR);		// shift out a trailing zero
	_delay_us(1.0);
	DRV_PORT |= _BV(DRV_DATA);
	DRV_PORT |= _BV(DRV_CS);		// end transmission
	return;
}

void shiftBuffer (void) {

	uint8_t i, j, val;
	
	DRV_PORT &= ~_BV(DRV_CS);		// enable the serial bus
	DRV_PORT &= ~_BV(DRV_WR);
	DRV_PORT |= _BV(DRV_WR);		// clock in a one
	DRV_PORT &= ~_BV(DRV_DATA);	// set data output to zero
	DRV_PORT &= ~_BV(DRV_WR);
	DRV_PORT |= _BV(DRV_WR);		// clock in a zero
	DRV_PORT |= _BV(DRV_DATA);
	DRV_PORT &= ~_BV(DRV_WR);
	DRV_PORT |= _BV(DRV_WR);		// clock in a one	
	DRV_PORT &= ~_BV(DRV_DATA);	// set data output to zero
	DRV_PORT &= ~_BV(DRV_WR);
	
	// set the address to 0x00
	for (i = 0; i < 7; i++)  {
		DRV_PORT &= ~_BV(DRV_WR);
		DRV_PORT |= _BV(DRV_WR);
	}
	
	// shift the data
	for (i = 0; i < 24; i++) {
		val = usiTwiReceiveByte();
		for (j = 0; j < 8; j++)  {
			DRV_PORT &= ~_BV(DRV_WR);	// prep for next bit
			if (val & (1 << j)) {
				DRV_PORT |= _BV(DRV_DATA);
			} else {
				DRV_PORT &= ~_BV(DRV_DATA);
			}
			DRV_PORT |= _BV(DRV_WR);	// clock in the next bit
		}
	}
	DRV_PORT |= _BV(DRV_WR);
	DRV_PORT |= _BV(DRV_DATA);
	DRV_PORT |= _BV(DRV_CS);		// end transmission
	return;

}

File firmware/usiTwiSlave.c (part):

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#  define DDR_USI             DDRB
#  define PORT_USI            PORTB
#  define PIN_USI             PINB
#  define PORT_USI_SDA        PB5
#  define PORT_USI_SCL        PB7
#  define PIN_USI_SDA         PINB5
#  define PIN_USI_SCL         PINB7
#  define USI_START_COND_INT  USISIF
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#  define DDR_USI             DDRB
#  define PORT_USI            PORTB
#  define PIN_USI             PINB
#  define PORT_USI_SDA        PB0
#  define PORT_USI_SCL        PB2
#  define PIN_USI_SDA         PINB0
#  define PIN_USI_SCL         PINB2
#  define USI_START_COND_INT  USISIF //was USICIF jjg
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#  define DDR_USI             DDRB
#  define PORT_USI            PORTB
#  define PIN_USI             PINB
#  define PORT_USI_SDA        PB0
#  define PORT_USI_SCL        PB2
#  define PIN_USI_SDA         PINB0
#  define PIN_USI_SCL         PINB2
#  define USI_START_COND_INT  USISIF
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#  define DDR_USI             DDRB
#  define PORT_USI            PORTB
#  define PIN_USI             PINB
#  define PORT_USI_SDA        PB0
#  define PORT_USI_SCL        PB2
#  define PIN_USI_SDA         PINB0
#  define PIN_USI_SCL         PINB2
#  define USI_START_COND_INT  USISIF
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
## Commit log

2013-06-07 Checking it all in for the first time
2013-06-10 Initial cleanup and minor fix to makefile
2013-12-27 updated .gitignore
2014-03-21 some small mods (nothing functional)
2014-03-21 Moved the board files back where they belong
2014-05-14 This is the new version, now with PWM!
2014-05-17 Final changes to get the firmware working.

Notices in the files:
firmware/usiTwiSlave.c:
This program is free software; you can redistribute it and/or modify it under the
terms of the GNU General Public License as published by the Free Software
rgb-matrix-backpack-4.brd:
Logos Electromechanical (c) 2012
CC-BY-NC-SA 3.0
rgb-matrix-backpack-5a.brd:
Logos Electromechanical (c) 2014
parts and their libraries:
dicons: Copyright (C) 2004, Bob Starr (rtzaudio@mindspring.com)
